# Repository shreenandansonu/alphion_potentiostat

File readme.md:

# ALPHION POTENTIOSTAT
<p align ="center">
    
</p>

## Overview

This Project is a basemodel for the ALPHION POTENTIOSTAT. Which is based on the research done at IITM by Bikash Kumar Mishra

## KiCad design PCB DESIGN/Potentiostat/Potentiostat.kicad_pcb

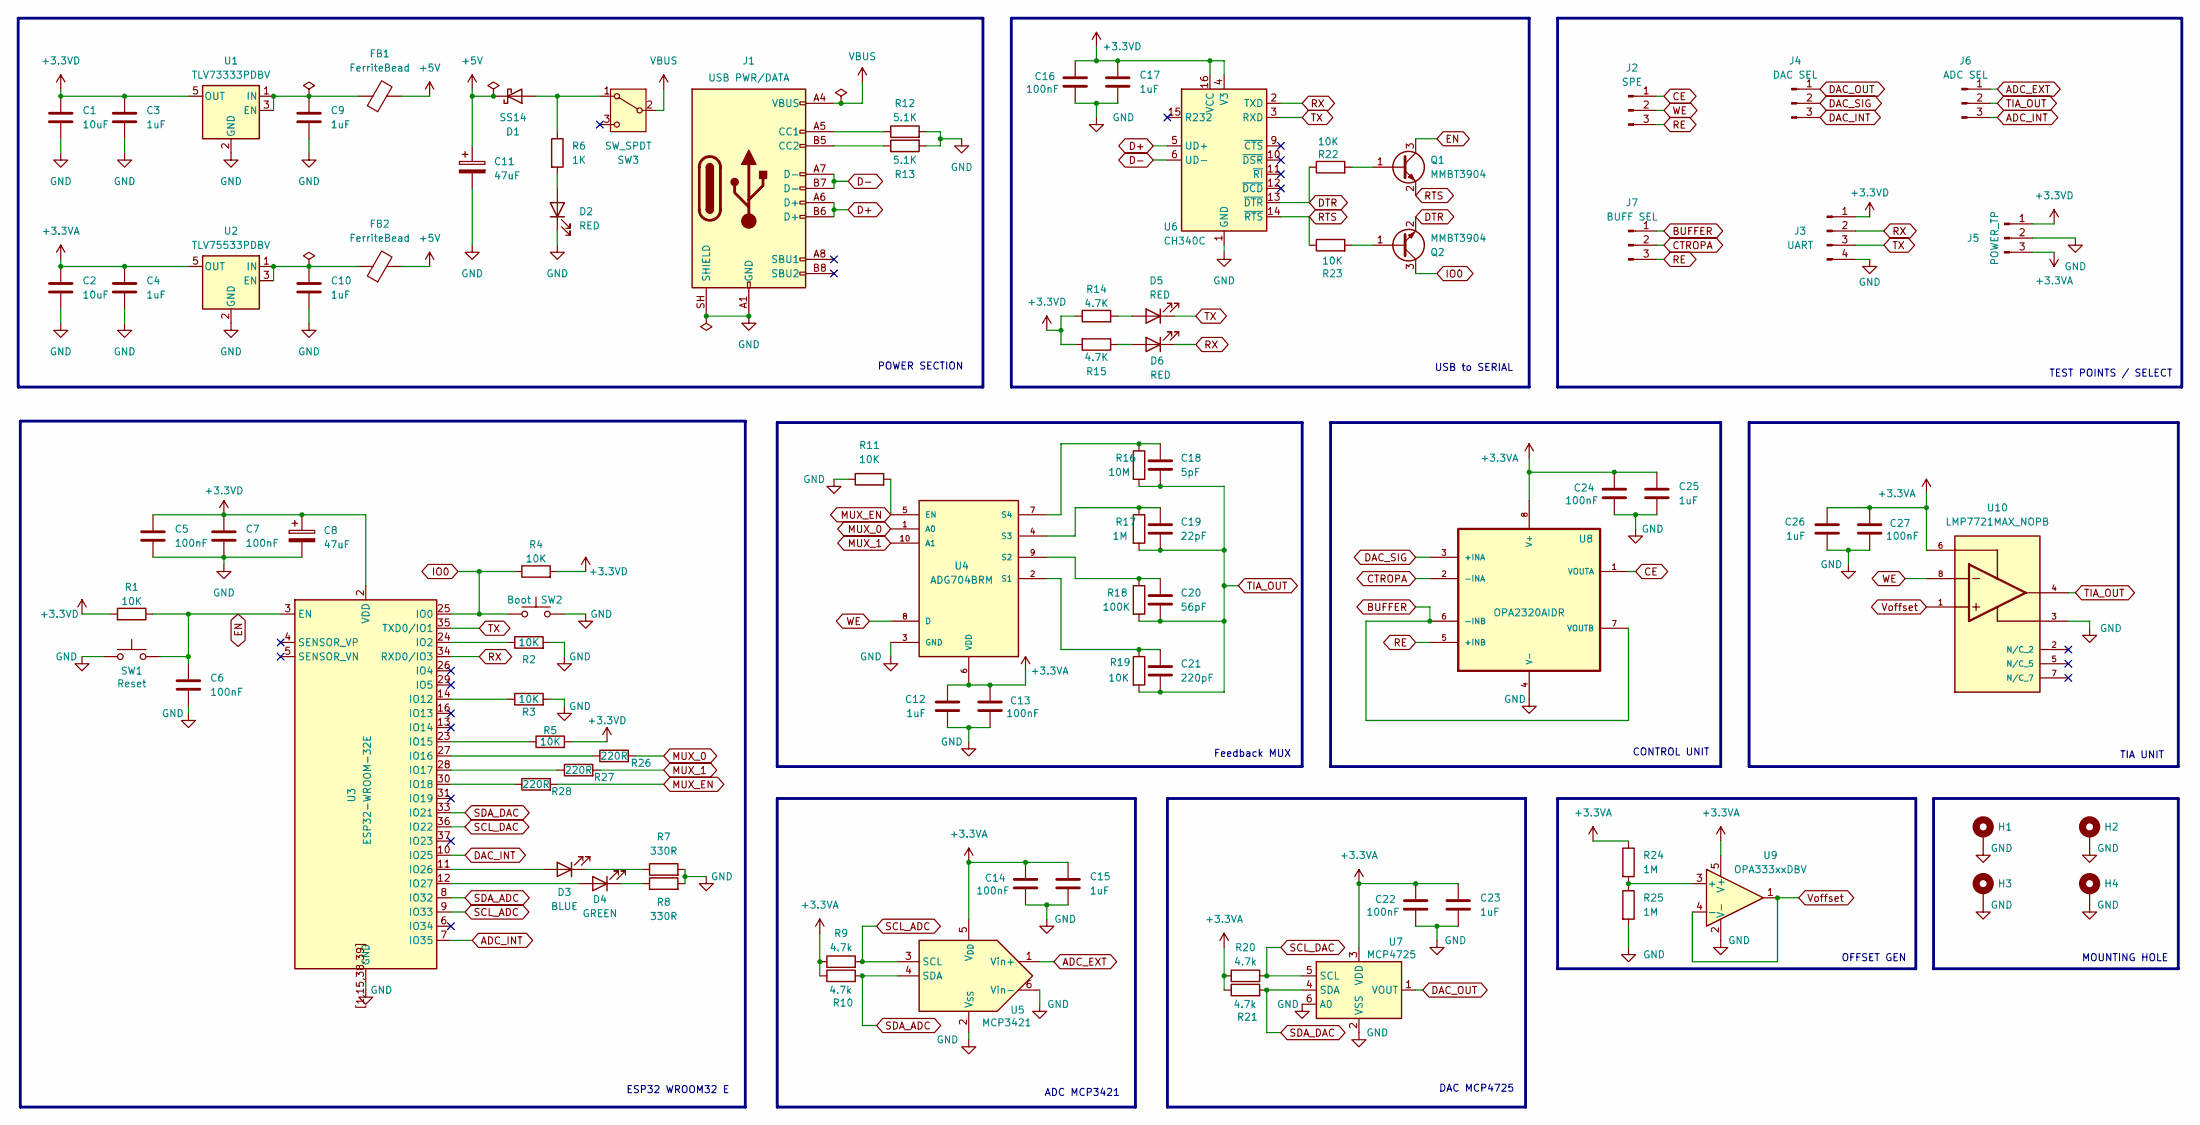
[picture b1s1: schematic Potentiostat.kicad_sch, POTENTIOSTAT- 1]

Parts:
C1, C2: 10uF; C_0805_2012Metric_Pad1.18x1.45mm_HandSolder
C3, C4, C9, C10, C12, C15, C17, C23, C25, C26: 1uF; C_0805_2012Metric_Pad1.18x1.45mm_HandSolder
C5, C6, C7, C13, C14, C16, C22, C24, C27: 100nF; C_0805_2012Metric_Pad1.18x1.45mm_HandSolder
C8, C11: 47uF; CP_Elec_6.3x5.8
C18: 5pF; C_0805_2012Metric_Pad1.18x1.45mm_HandSolder
C19: 22pF; C_0805_2012Metric_Pad1.18x1.45mm_HandSolder
C20: 56pF; C_0805_2012Metric_Pad1.18x1.45mm_HandSolder
C21: 220pF; C_0805_2012Metric_Pad1.18x1.45mm_HandSolder
D1: SS14; D_SMA
D2, D5, D6: RED; LED_0805_2012Metric_Pad1.15x1.40mm_HandSolder
D3: BLUE; LED_0805_2012Metric_Pad1.15x1.40mm_HandSolder
D4: GREEN; LED_0805_2012Metric_Pad1.15x1.40mm_HandSolder
FB1, FB2: FerriteBead; R_0805_2012Metric_Pad1.20x1.40mm_HandSolder
H1, H2, H3, H4: MountingHole_2.5mm_Pad
J1: USB PWR/DATA; USB_C_Receptacle_HRO_TYPE-C-31-M-12
J2: SPE; PinHeader_1x03_P2.54mm_Vertical
J3: UART; PinHeader_1x04_P2.54mm_Vertical
J4: DAC SEL; PinHeader_1x03_P2.54mm_Vertical
J5: POWER_TP; PinHeader_1x03_P2.54mm_Vertical
J6: ADC SEL; PinHeader_1x03_P2.54mm_Vertical
J7: BUFF SEL; PinHeader_1x03_P2.54mm_Vertical
Q1, Q2: MMBT3904; SOT-23
R1, R2, R3, R4, R5, R11, R19, R22, R23: 10K; R_0805_2012Metric_Pad1.20x1.40mm_HandSolder
R6: 1K; R_0805_2012Metric_Pad1.20x1.40mm_HandSolder
R7, R8: 330R; R_0805_2012Metric_Pad1.20x1.40mm_HandSolder
R9, R10, R20, R21: 4.7k; R_0805_2012Metric_Pad1.20x1.40mm_HandSolder
R12, R13: 5.1K; R_0805_2012Metric_Pad1.20x1.40mm_HandSolder
R14, R15: 4.7K; R_0805_2012Metric_Pad1.20x1.40mm_HandSolder
R16: 10M; R_0805_2012Metric_Pad1.20x1.40mm_HandSolder
R17, R24, R25: 1M; R_0805_2012Metric_Pad1.20x1.40mm_HandSolder
R18: 100K; R_0805_2012Metric_Pad1.20x1.40mm_HandSolder
R26, R27, R28: 220R; R_0805_2012Metric_Pad1.20x1.40mm_HandSolder
SW1: Reset; SW_Push_1P1T_NO_CK_KSC7xxJ
SW2: Boot; SW_Push_1P1T_NO_CK_KSC7xxJ
SW3: SW_SPDT; SW_Slide_SPDT_Angled_CK_OS102011MA1Q
U1: TLV73333PDBV; SOT-23-5
U2: TLV75533PDBV; SOT-23-5
U3: ESP32-WROOM-32E
U4: ADG704BRM; MSOP10
U5: MCP3421; SOT-23-6
U6: CH340C; SOIC-16_3.9x9.9mm_P1.27mm
U7: MCP4725; SOT-23-6_Handsoldering
U8: OPA2320AIDR; SOIC127P599X175-8N
U9: OPA333xxDBV; SOT-23-5
U10: LMP7721MAX_NOPB; SOIC127P599X175-8N; PARTREV E

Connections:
+3.3VA: C2.1, C4.1, C12.1, C13.1, C14.1, C15.1, C22.1, C23.1, C24.1, C25.1, C26.1, C27.1, J5.3, R9.1, R10.1, R20.1, R21.1, R24.1, U2.5 (OUT), U4.6 (VDD), U5.5 (V_{DD}), U7.3 (VDD), U8.8 (V+), U9.5 (V+), U10.6
+3.3VD: C1.1, C3.1, C5.1, C7.1, C8.1, C16.1, C17.1, J3.1, J5.1, R1.2, R4.2, R5.2, R14.1, R15.2, U1.5 (OUT), U3.2 (VDD), U6.4 (V3), U6.16 (VCC)
+5V: C11.1, D1.1 (K), FB1.2, FB2.2
ADC_EXT: J6.1, U5.1 (Vin+)
ADC_INT: J6.3, U3.7 (IO35)
BUFFER: J7.1, U8.6 (-INB), U8.7 (VOUTB)
CE: J2.1, U8.1 (VOUTA)
CTROPA: J7.2, U8.2 (-INA)
D+: J1.A6 (D+), J1.B6 (D+), U6.5 (UD+)
D-: J1.A7 (D-), J1.B7 (D-), U6.6 (UD-)
DAC_INT: J4.3, U3.10 (IO25)
DAC_OUT: J4.1, U7.1 (VOUT)
DAC_SIG: J4.2, U8.3 (+INA)
DTR: Q2.2 (E), R22.1, U6.13 (~DTR)
EN: C6.1, Q1.3 (C), R1.1, SW1.1, U3.3 (EN)
GND: C1.2, C2.2, C3.2, C4.2, C5.2, C6.2, C7.2, C8.2, C9.2, C10.2, C11.2, C12.2, C13.2, C14.2, C15.2, C16.2, C17.2, C22.2, C23.2, C24.2, C25.2, C26.2, C27.2, D2.1 (K), H1.1 (1_1), H2.1 (1_1), H3.1 (1_1), H4.1 (1_1), J1.A1 (GND), J1.A12 (GND), J1.B1 (GND), J1.B12 (GND), J1.SH (SHIELD), J3.4, J5.2, R2.2, R3.2, R7.2, R8.2, R11.1, R12.2, R13.2, R25.2, SW1.2, SW2.1, U1.2 (GND), U2.2 (GND), U3.1 (GND), U3.15 (GND), U3.38 (GND), U3.39 (GND), U3.[1,15,38,39] (GND), U4.3 (GND), U5.2 (V_{SS}), U5.6 (Vin-), U6.1 (GND), U7.2 (VSS), U7.6 (A0), U8.4 (V-), U9.2 (V-), U10.3
IO0: Q2.3 (C), R4.1, SW2.2, U3.25 (IO0)
MUX_0: R26.2, U4.1 (A0)
MUX_1: R27.2, U4.10 (A1)
MUX_EN: R11.2, R28.2, U4.5 (EN)
unnamed: D1.2 (A), R6.1, SW3.1 (A)
unnamed: D2.2 (A), R6.2
unnamed: D3.2 (A), U3.11 (IO26)
unnamed: D3.1 (K), R7.1
unnamed: D4.2 (A), U3.12 (IO27)
unnamed: D4.1 (K), R8.1
unnamed: D5.2 (A), R14.2
unnamed: D6.2 (A), R15.1
unnamed: J1.A5 (CC1), R12.1
unnamed: J1.B5 (CC2), R13.1
unnamed: Q1.1 (B), R22.2
unnamed: Q2.1 (B), R23.2
unnamed: C9.1, FB1.1, U1.1 (IN), U1.3 (EN)
unnamed: C10.1, FB2.1, U2.1 (IN), U2.3 (EN)
unnamed: R2.1, U3.24 (IO2)
unnamed: R3.1, U3.14 (IO12)
unnamed: R5.1, U3.23 (IO15)
unnamed: R26.1, U3.27 (IO16)
unnamed: R27.1, U3.28 (IO17)
unnamed: R28.1, U3.30 (IO18)
unnamed: C21.1, R19.1, U4.2 (S1)
unnamed: C20.1, R18.1, U4.9 (S2)
unnamed: C19.1, R17.1, U4.4 (S3)
unnamed: C18.1, R16.1, U4.7 (S4)
unnamed: R24.2, R25.1, U9.3 (+)
RE: J2.3, J7.3, U8.5 (+INB)
RTS: Q1.2 (E), R23.1, U6.14 (~RTS)
RX: D6.1 (K), J3.2, U3.34 (RXD0/IO3), U6.2 (TXD)
SCL_ADC: R9.2, U3.9 (IO33), U5.3 (SCL)
SCL_DAC: R20.2, U3.36 (IO22), U7.5 (SCL)
SDA_ADC: R10.2, U3.8 (IO32), U5.4 (SDA)
SDA_DAC: R21.2, U3.33 (IO21), U7.4 (SDA)
TIA_OUT: C18.2, C19.2, C20.2, C21.2, J6.2, R16.2, R17.2, R18.2, R19.2, U10.4
TX: D5.1 (K), J3.3, U3.35 (TXD0/IO1), U6.3 (RXD)
VBUS: J1.A4 (VBUS), J1.A9 (VBUS), J1.B4 (VBUS), J1.B9 (VBUS), SW3.2 (B)
Voffset: U9.1, U9.4 (-), U10.1
WE: J2.2, U4.8 (D), U10.8

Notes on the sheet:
TIA UNIT
CONTROL UNIT
TEST POINTS / SELECT
ESP32 WROOM32 E
MOUNTING HOLE
ADC MCP3421
Feedback MUX
DAC MCP4725
OFFSET GEN
POWER SECTION
USB to SERIAL

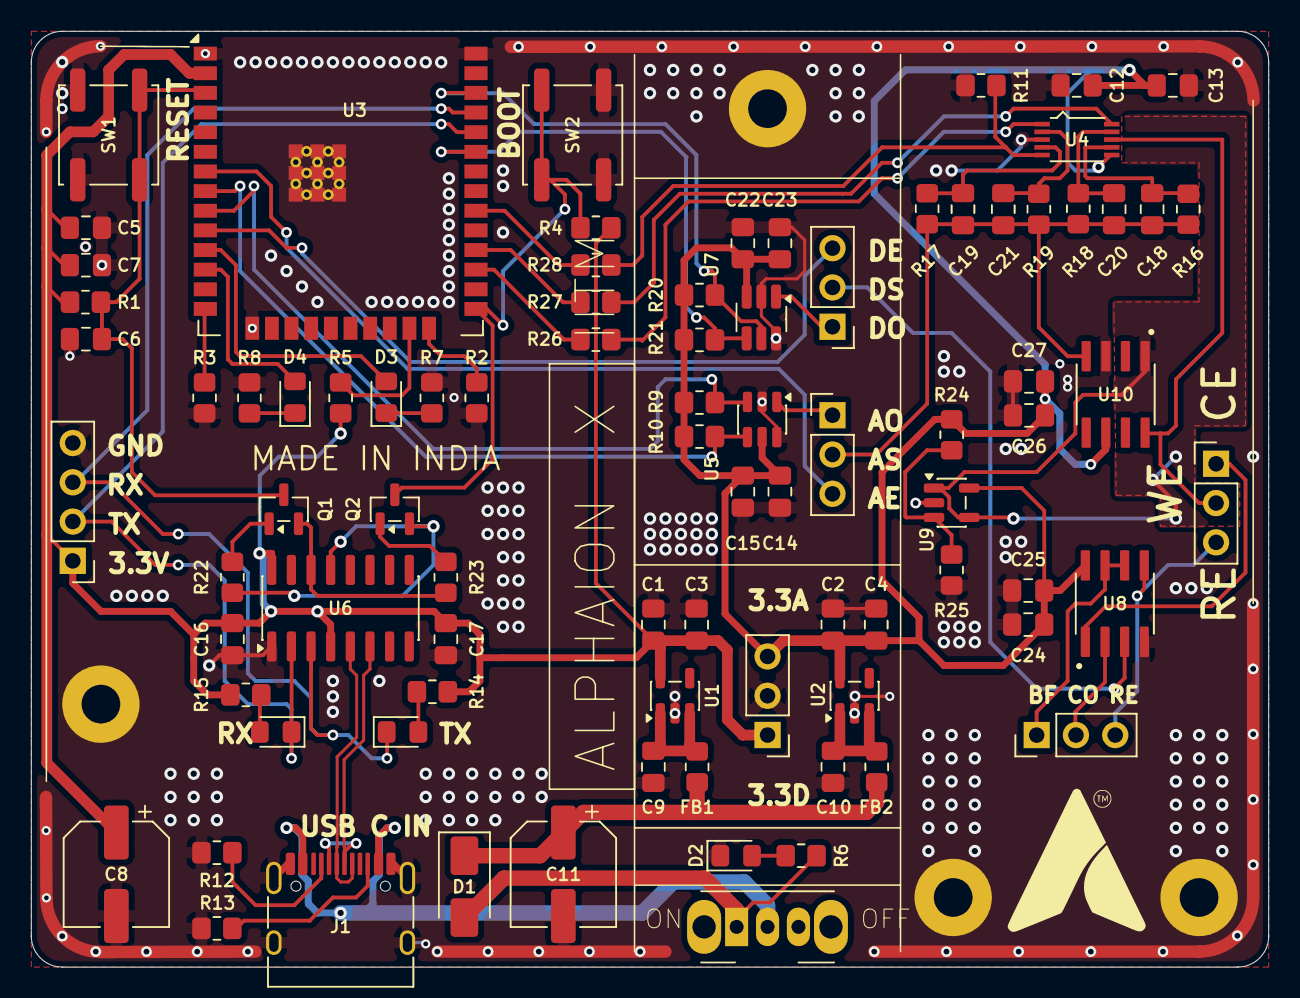
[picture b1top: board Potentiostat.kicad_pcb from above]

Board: 2 copper layers, 80.0 x 60.5 mm, 89 parts (0 on the bottom side), 57 nets.

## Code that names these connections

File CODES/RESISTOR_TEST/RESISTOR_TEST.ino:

#include <Wire.h>
#include <math.h>

// =====================================================
// 10K RESISTOR POTENTIOSTAT TEST
// ESP32 + MCP4725 + MCP3421 + ADG704
// =====================================================

// ---------------- DAC ----------------
#define DAC_SDA       21
#define DAC_SCL       22
#define DAC_ADDR      0x60

// ---------------- ADC ----------------
#define ADC_SDA       32
#define ADC_SCL       33
#define ADC_ADDR      0x68

// ---------------- MUX ----------------
#define MUX_0         16
#define MUX_1         17
#define MUX_EN        18

TwoWire DAC_Wire = TwoWire(0);
TwoWire ADC_Wire = TwoWire(1);

// =====================================================
// USER SETTINGS
// =====================================================

// Update these to measured board values if available.
const float DAC_SUPPLY = 3.30;
const float V_OFFSET   = 1.65;

// Feedback resistor selected by MUX S1
const float R_FEEDBACK = 10000.0;

// Test sweep
const float DAC_MIN_V = 1.45;
const float DAC_MAX_V = 1.85;

// DAC increment in 12-bit counts
const int DAC_STEP = 4;

// Delay after changing DAC
const int SETTLE_DELAY_MS = 5;

// Ignore resistance calculations near zero current
const float MIN_CURRENT_uA = 2.0;
const float MIN_DRIVE_V = 0.02;

// MCP3421 single-shot, 12-bit, PGA x1
// RDY=1 starts conversion; MD=0; S1:S0=00; PGA=00
const uint8_t ADC_START_CONFIG = 0x80;

// =====================================================
// DAC FUNCTIONS
// =====================================================

uint16_t voltageToDAC(float voltage)
{
    voltage = constrain(voltage, 0.0, DAC_SUPPLY);

    return (uint16_t)round(
        voltage * 4095.0 / DAC_SUPPLY
    );
}

bool writeDAC(uint16_t value)
{
    value = constrain(value, 0, 4095);

    DAC_Wire.beginTransmission(DAC_ADDR);
    DAC_Wire.write(0x40);
    DAC_Wire.write(value >> 4);
    DAC_Wire.write((value & 0x0F) << 4);

    return DAC_Wire.endTransmission() == 0;
}

// =====================================================
// MUX CONTROL
// ADG704: A1=0, A0=0 selects S1
// EN is active HIGH
// =====================================================

void select10KFeedback()
{
    digitalWrite(MUX_EN, LOW);
    delay(2);

    digitalWrite(MUX_0, LOW);
    digitalWrite(MUX_1, LOW);

    delay(2);

    digitalWrite(MUX_EN, HIGH);
    delay(10);
}

// =====================================================
// MCP3421 ADC
// 12-bit, single-shot, PGA x1
// LSB = 1mV
// =====================================================

bool readADC(float &voltage)
{
    // Start conversion
    ADC_Wire.beginTransmission(ADC_ADDR);
    ADC_Wire.write(ADC_START_CONFIG);

    if (ADC_Wire.endTransmission() != 0)
        return false;

    unsigned long startTime = millis();

    while (millis() - startTime < 100)
    {
        uint8_t count = ADC_Wire.requestFrom(
            (uint8_t)ADC_ADDR,
            (uint8_t)3
        );

        if (count == 3)
        {
            uint8_t msb = ADC_Wire.read();
            uint8_t lsb = ADC_Wire.read();
            uint8_t config = ADC_Wire.read();

            // RDY = 0 means conversion completed
            if ((config & 0x80) == 0)
            {
                int16_t raw =
                    ((uint16_t)msb << 8) | lsb;

                // Extract signed 12-bit result
                raw &= 0x0FFF;

                if (raw & 0x0800)
                    raw |= 0xF000;

                voltage = raw * 0.001f;

                return true;
            }
        }

        delay(1);
    }

    return false;
}

// =====================================================
// MEASUREMENT
// =====================================================

void takeMeasurement(uint16_t dacCode)
{
    float tiaVoltage = NAN;

    float dacVoltage =
        (dacCode / 4095.0f) * DAC_SUPPLY;

    // Update DAC
    if (!writeDAC(dacCode))
    {
        Serial.println("ERROR,DAC_WRITE");
        return;
    }

    // Allow analog circuit to settle
    delay(SETTLE_DELAY_MS);

    // Read TIA output
    if (!readADC(tiaVoltage))
    {
        Serial.println("ERROR,ADC_READ");
        return;
    }

    // TIA current:
    // I = (V_OFFSET - TIA_OUT) / R_FEEDBACK
    float current_uA =
        ((V_OFFSET - tiaVoltage) / R_FEEDBACK)
        * 1000000.0f;

    // Assumed voltage across the test resistor
    float driveVoltage = dacVoltage - V_OFFSET;

    // Calculate resistance only away from zero crossing
    float estimatedResistance = NAN;

    if (fabs(driveVoltage) >= MIN_DRIVE_V &&
        fabs(current_uA) >= MIN_CURRENT_uA)
    {
        estimatedResistance =
            fabs(driveVoltage / (current_uA / 1000000.0f));
    }

    // CSV:
    // TIME_MS,DAC_CODE,DAC_V,TIA_V,CURRENT_uA,EST_R_OHM

    Serial.print(millis());
    Serial.print(",");

    Serial.print(dacCode);
    Serial.print(",");

    Serial.print(dacVoltage, 5);
    Serial.print(",");

    Serial.print(tiaVoltage, 5);
    Serial.print(",");

    Serial.print(current_uA, 3);
    Serial.print(",");

    if (isnan(estimatedResistance))
        Serial.println("nan");
    else
        Serial.println(estimatedResistance, 1);
}

// =====================================================
// SETUP
// =====================================================

void setup()
{
    Serial.begin(230400);
    delay(1000);

    pinMode(MUX_0, OUTPUT);
    pinMode(MUX_1, OUTPUT);
    pinMode(MUX_EN, OUTPUT);

    digitalWrite(MUX_EN, LOW);

    DAC_Wire.begin(DAC_SDA, DAC_SCL);
    ADC_Wire.begin(ADC_SDA, ADC_SCL);

    DAC_Wire.setClock(100000);
    ADC_Wire.setClock(100000);

    select10KFeedback();

    // Start at offset
    writeDAC(voltageToDAC(V_OFFSET));

    delay(100);

    Serial.println(
        "TIME_MS,DAC_CODE,DAC_V,TIA_V,CURRENT_uA,EST_R_OHM"
    );
}

// =====================================================
// TRIANGULAR SWEEP
// =====================================================

void loop()
{
    uint16_t minCode = voltageToDAC(DAC_MIN_V);
    uint16_t maxCode = voltageToDAC(DAC_MAX_V);

    // Rising sweep
    for (uint16_t code = minCode;
         code <= maxCode;
         code += DAC_STEP)
    {
        takeMeasurement(code);
    }

    takeMeasurement(maxCode);

    // Falling sweep
    int32_t code = (int32_t)maxCode - DAC_STEP;

    while (code >= minCode)
    {
        takeMeasurement((uint16_t)code);
        code -= DAC_STEP;
    }

    takeMeasurement(minCode);
}
